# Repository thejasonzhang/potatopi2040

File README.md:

PotatoPi
Overview

PotatoPi is a custom RP2040-based devboard that can be used for lots of cool hardware and software projects.
It follows the same pinout as the Raspberry Pi Pico and is fully feature-compatible.

It will also include headers soldered on.

- Features
- 16MB onboard flash memory
- Convenient reset button for easy flashing
- Custom PotatoPi artwork on both sides of the PCB
- All components hand soldered (no PCBA)

I made this to get back into hardware and to redeem myself from my last project.
I also wanted to try out SMD soldering.
The board will use a hot plate to do most of the reflow work and then an iron to fix any mistakes and add the ehaders.

Gallery

Front & board renders as well as Potato Pi illustrations:

Bill of Materials (BOM)

| **Category** | **Designator / Item** | **Footprint / Description** | **Qty** | **Value / Part** | **Link**                                                                                                 | **Cost** |
| ------------ | --------------------- | --------------------------- | ------- | ---------------- | -------------------------------------------------------------------------------------------------------- | -------- |
| Capacitor    | C1, C12               | 402                         | 2       | 1µF              | [https://www.lcsc.com/product-detail/C29266.html](https://www.lcsc.com/product-detail/C29266.html)       | 0.26     |
| Capacitor    | C10–C11, C17, C2–C9   | 402                         | 11      | 0.1µF            | [https://www.lcsc.com/product-detail/C1525.html](https://www.lcsc.com/product-detail/C1525.html)         | 0.13     |
| Capacitor    | C13, C14              | 603                         | 2       | 10µF             | [https://www.lcsc.com/product-detail/C19702.html](https://www.lcsc.com/product-detail/C19702.html)       | 0.40     |
| Capacitor    | C15, C16              | 603                         | 2       | 33pF             | [https://www.lcsc.com/product-detail/C107047.html](https://www.lcsc.com/product-detail/C107047.html)     | 0.30     |
| Connector    | J1                    | USB-C Receptacle            | 1       | USB 2.0 14P      | [https://www.lcsc.com/product-detail/C165948.html](https://www.lcsc.com/product-detail/C165948.html)     | 0.85     |
| Connector    | J2, J3                | Pin Header 1x20             | 2       | Conn_01x20       | [https://www.lcsc.com/product-detail/C42431804.html](https://www.lcsc.com/product-detail/C42431804.html) | 0.46     |
| Connector    | J4                    | Pin Header 1x03             | 1       | Conn_01x03       | [https://www.lcsc.com/product-detail/C32713269.html](https://www.lcsc.com/product-detail/C32713269.html) | 0.11     |
| Resistor     | R1, R2                | 402                         | 2       | 5.1kΩ            | [https://www.lcsc.com/product-detail/C25905.html](https://www.lcsc.com/product-detail/C25905.html)       | 0.08     |
| Resistor     | R3, R4                | 402                         | 2       | 27Ω              | [https://www.lcsc.com/product-detail/C25100.html](https://www.lcsc.com/product-detail/C25100.html)       | 0.08     |
| Resistor     | R5, R6                | 402                         | 2       | 1kΩ              | [https://www.lcsc.com/product-detail/C11702.html](https://www.lcsc.com/product-detail/C11702.html)       | 0.07     |
| Resistor     | R7                    | 402                         | 1       | 10kΩ             | [https://www.lcsc.com/product-detail/C60490.html](https://www.lcsc.com/product-detail/C60490.html)       | 0.08     |
| Switch       | SW1                   | Push Button                 | 1       | Momentary        | [https://www.lcsc.com/product-detail/C720477.html](https://www.lcsc.com/product-detail/C720477.html)     | 0.55     |
| IC           | U1                    | QFN-56                      | 1       | RP2040           | [https://www.lcsc.com/product-detail/C2040.html](https://www.lcsc.com/product-detail/C2040.html)         | 0.95     |
| IC           | U2                    | SOT-23                      | 1       | MCP1700-3302     | [https://www.lcsc.com/product-detail/C39051.html](https://www.lcsc.com/product-detail/C39051.html)       | 2.45     |
| IC           | U3                    | USON-8                      | 1       | W25Q16JV         | [https://www.lcsc.com/product-detail/C2456208.html](https://www.lcsc.com/product-detail/C2456208.html)   | 1.31     |
| Crystal      | Y1                    | 3225                        | 1       | 12 MHz           | [https://www.lcsc.com/product-detail/C9002.html](https://www.lcsc.com/product-detail/C9002.html)         | 0.73     |
| Service      | PCB                   | JLCPCB fabrication          | 1       | Manufacturing    | [https://cart.jlcpcb.com/quote/gerberviewThree/?qs=d00311a2c2824fc7aa7ee1bc072ff726_1_0_1_0_0.html]                                                                                                     | 2.10     |
| Tool         | Tip                   | T18-D24 solder tip          | 1       | Hakko chisel     | [https://www.microcenter.com/product/658966/hakko-t18-series-006-in-chisel-tip]                                                                                            | 6.99     |
| Tool         | Wick                  | Desolder wick               | 1       | iFixit wick      |[https://www.microcenter.com/product/693022/ifixit-desoldering-wick]                                                                                            | 4.99     |
| Tool         | Tweezers              | Curved ESD                  | 1       | precision        | [https://www.microcenter.com/product/361636/enkay-products-heat-resistant-soldering-tweezers-curved-point]                                                                                             | 2.99     |
| Tool         | Helping Hand          | Magnifier stand             | 1       | third hand       |[https://www.microcenter.com/product/618902/inland-inland-adjustable-helping-hand-w-magnifying-glass]                                                                                             | 4.99     |
Cost Summary
Subtotal: $30.87
Shipping: $15.24
Tax: $3.82
TOTAL: $49.93

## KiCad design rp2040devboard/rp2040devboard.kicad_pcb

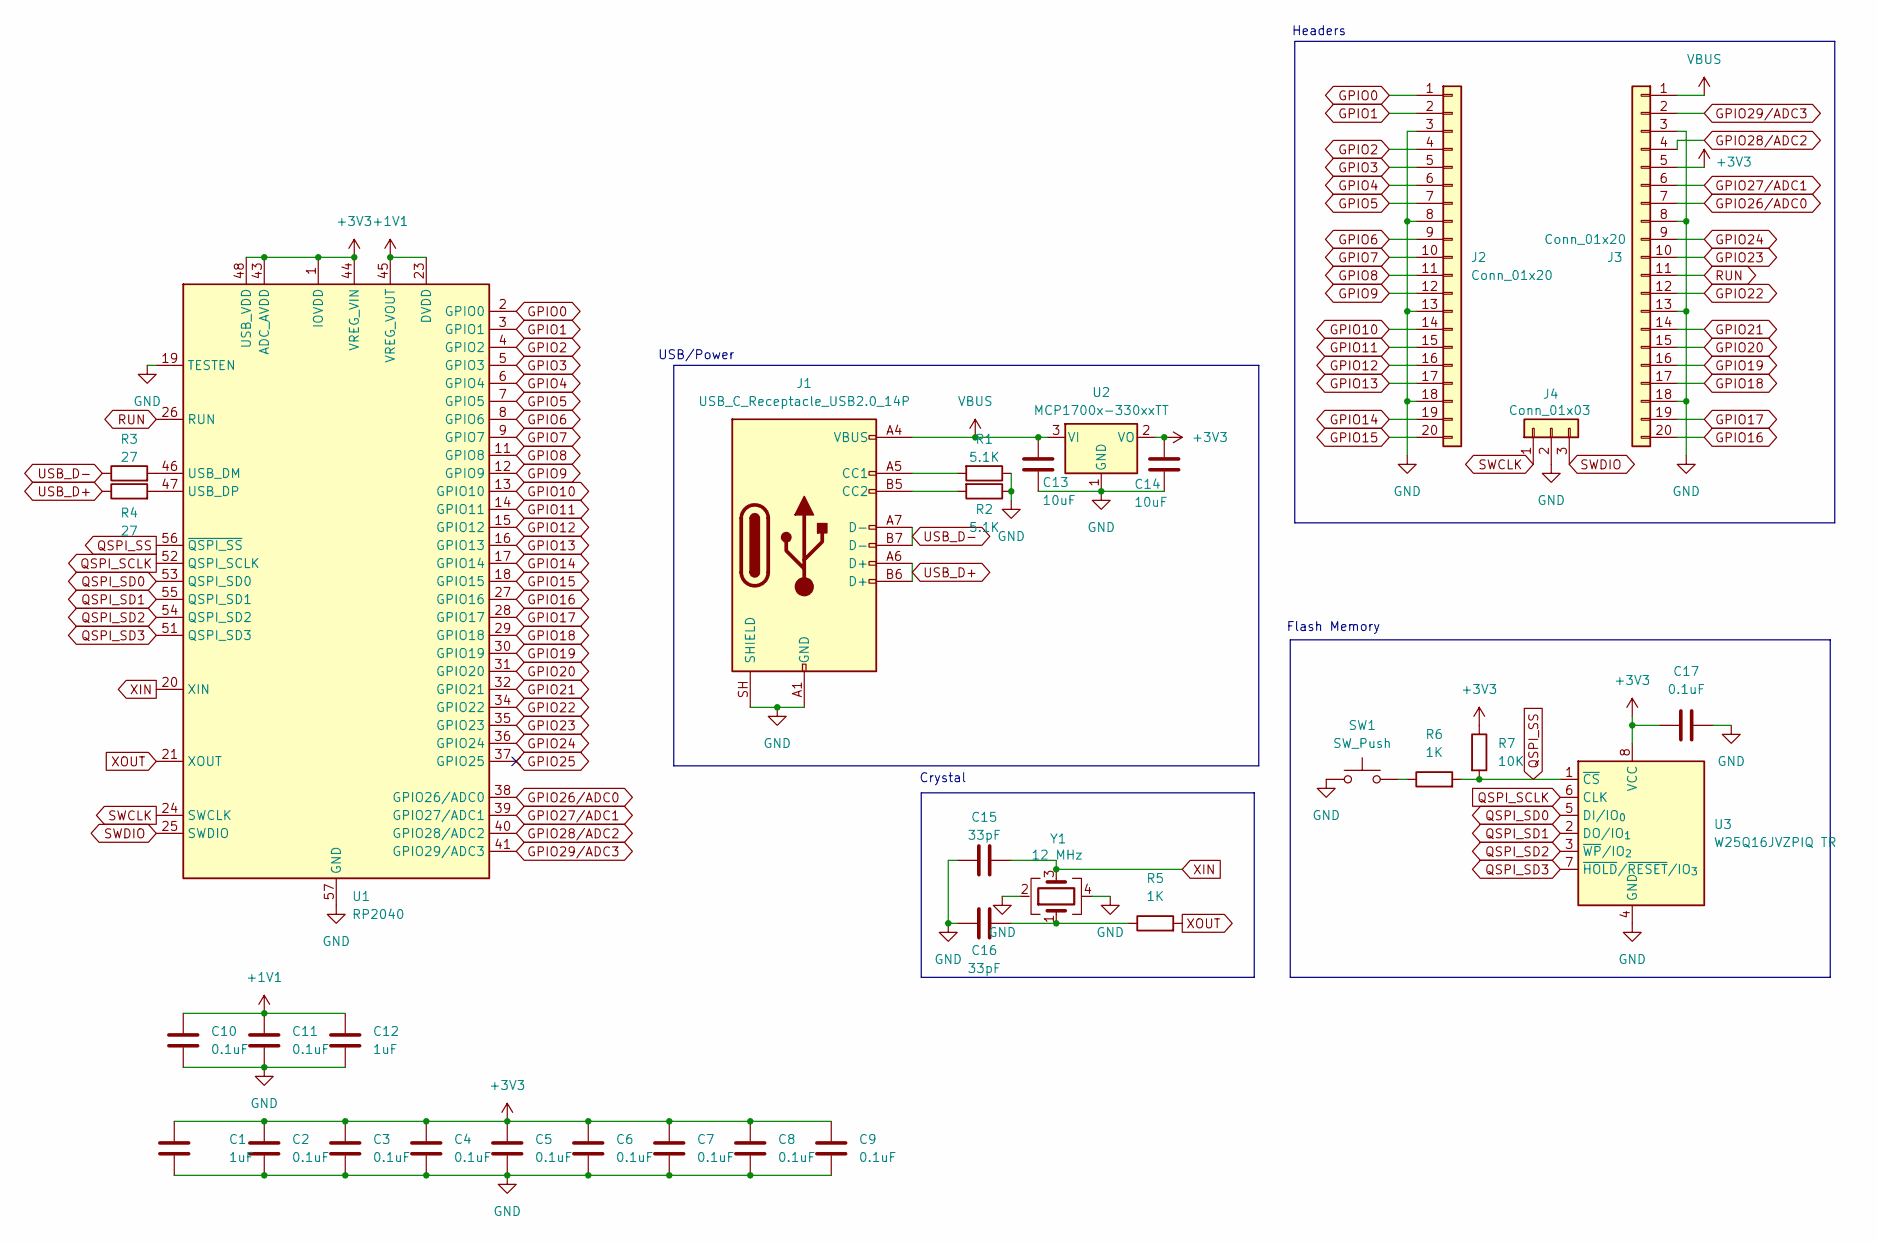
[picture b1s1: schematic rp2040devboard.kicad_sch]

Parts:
C1, C12: 1uF; C_0402_1005Metric
C2, C3, C4, C5, C6, C7, C8, C9, C10, C11, C17: 0.1uF; C_0402_1005Metric
C13, C14: 10uF; C_0603_1608Metric
C15, C16: 33pF; C_0603_1608Metric
J1: USB_C_Receptacle_USB2.0_14P; USB_C_Receptacle_HRO_TYPE-C-31-M-12
J2, J3: Conn_01x20; PinHeader_1x20_P2.54mm_Vertical
J4: Conn_01x03; PinHeader_1x03_P2.54mm_Vertical
R1, R2: 5.1K; R_0402_1005Metric
R3, R4: 27; R_0402_1005Metric
R5, R6: 1K; R_0402_1005Metric
R7: 10K; R_0402_1005Metric
SW1: SW_Push; SW_Push_SPST_NO_Alps_SKRK
U1: RP2040; QFN-56-1EP_7x7mm_P0.4mm_EP3.2x3.2mm
U2: MCP1700x-330xxTT; SOT-23
U3: W25Q16JVZPIQ TR; Winbond_USON-8-1EP_3x2mm_P0.5mm_EP0.2x1.6mm
Y1: 12 MHz; Crystal_SMD_3225-4Pin_3.2x2.5mm

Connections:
+1V1: C10.1, C11.1, C12.1, U1.23 (DVDD), U1.45 (VREG_VOUT), U1.50 (DVDD)
+3V3: C1.1, C2.1, C3.1, C4.1, C5.1, C6.1, C7.1, C8.1, C9.1, C14.1, C17.2, J3.5, R7.1, U1.1 (IOVDD), U1.10 (IOVDD), U1.22 (IOVDD), U1.33 (IOVDD), U1.42 (IOVDD), U1.43 (ADC_AVDD), U1.44 (VREG_VIN), U1.48 (USB_VDD), U1.49 (IOVDD), U2.2 (VO), U3.8 (VCC)
GND: C1.2, C2.2, C3.2, C4.2, C5.2, C6.2, C7.2, C8.2, C9.2, C10.2, C11.2, C12.2, C13.1, C14.2, C15.1, C16.1, C17.1, J1.A1 (GND), J1.A12 (GND), J1.B1 (GND), J1.B12 (GND), J1.SH (SHIELD), J2.3, J2.8, J2.13, J2.18, J3.3, J3.8, J3.13, J3.18, J4.2, R1.1, R2.1, SW1.1, U1.19 (TESTEN), U1.57 (GND), U2.1 (GND), U3.4 (GND), Y1.2 (G), Y1.4 (G)
GPIO0: J2.1, U1.2 (GPIO0)
GPIO1: J2.2, U1.3 (GPIO1)
GPIO2: J2.4, U1.4 (GPIO2)
GPIO3: J2.5, U1.5 (GPIO3)
GPIO4: J2.6, U1.6 (GPIO4)
GPIO5: J2.7, U1.7 (GPIO5)
GPIO6: J2.9, U1.8 (GPIO6)
GPIO7: J2.10, U1.9 (GPIO7)
GPIO8: J2.11, U1.11 (GPIO8)
GPIO9: J2.12, U1.12 (GPIO9)
GPIO10: J2.14, U1.13 (GPIO10)
GPIO11: J2.15, U1.14 (GPIO11)
GPIO12: J2.16, U1.15 (GPIO12)
GPIO13: J2.17, U1.16 (GPIO13)
GPIO14: J2.19, U1.17 (GPIO14)
GPIO15: J2.20, U1.18 (GPIO15)
GPIO16: J3.20, U1.27 (GPIO16)
GPIO17: J3.19, U1.28 (GPIO17)
GPIO18: J3.17, U1.29 (GPIO18)
GPIO19: J3.16, U1.30 (GPIO19)
GPIO20: J3.15, U1.31 (GPIO20)
GPIO21: J3.14, U1.32 (GPIO21)
GPIO22: J3.12, U1.34 (GPIO22)
GPIO23: J3.10, U1.35 (GPIO23)
GPIO24: J3.9, U1.36 (GPIO24)
GPIO25: U1.37 (GPIO25)
GPIO26/ADC0: J3.7, U1.38 (GPIO26/ADC0)
GPIO27/ADC1: J3.6, U1.39 (GPIO27/ADC1)
GPIO28/ADC2: J3.4, U1.40 (GPIO28/ADC2)
GPIO29/ADC3: J3.2, U1.41 (GPIO29/ADC3)
unnamed: C16.2, R5.1, Y1.1
unnamed: J1.A5 (CC1), R1.2
unnamed: J1.B5 (CC2), R2.2
unnamed: R6.1, SW1.2
unnamed: R3.2, U1.46 (USB_DM)
unnamed: R4.2, U1.47 (USB_DP)
QSPI_SCLK: U1.52 (QSPI_SCLK), U3.6 (CLK)
QSPI_SD0: U1.53 (QSPI_SD0), U3.5 (DI/IO_{0})
QSPI_SD1: U1.55 (QSPI_SD1), U3.2 (DO/IO_{1})
QSPI_SD2: U1.54 (QSPI_SD2), U3.3 (~WP/IO_{2})
QSPI_SD3: U1.51 (QSPI_SD3), U3.7 (~HOLD/~RESET/IO_{3})
QSPI_SS: R6.2, R7.2, U1.56 (~QSPI_SS), U3.1 (~CS)
RUN: J3.11, U1.26 (RUN)
SWCLK: J4.1, U1.24 (SWCLK)
SWDIO: J4.3, U1.25 (SWDIO)
USB_D+: J1.A6 (D+), J1.B6 (D+), R4.1
USB_D-: J1.A7 (D-), J1.B7 (D-), R3.1
VBUS: C13.2, J1.A4 (VBUS), J1.A9 (VBUS), J1.B4 (VBUS), J1.B9 (VBUS), J3.1, U2.3 (VI)
XIN: C15.2, U1.20 (XIN), Y1.3
XOUT: R5.2, U1.21 (XOUT)

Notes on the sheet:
USB/Power
Crystal
Flash Memory
Headers

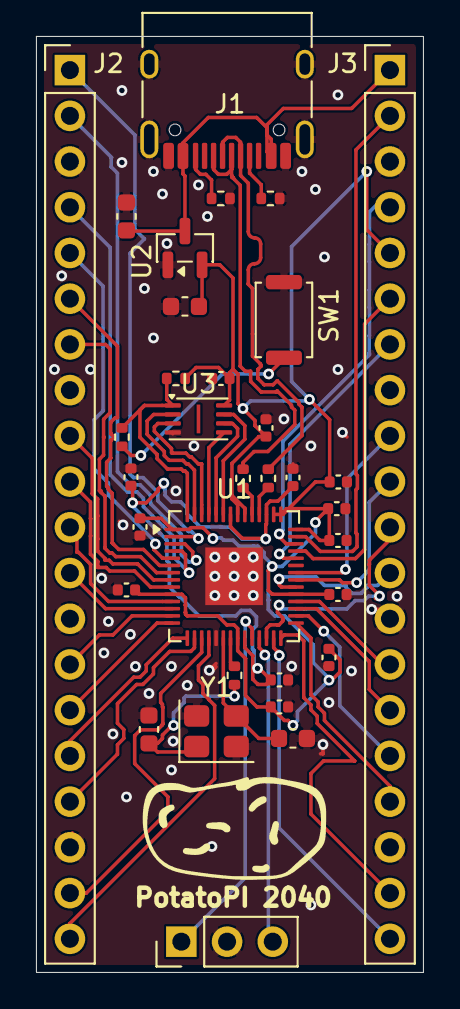
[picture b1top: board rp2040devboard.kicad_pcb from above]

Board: 2 copper layers, 21.5 x 52.0 mm, 33 parts (0 on the bottom side), 52 nets.

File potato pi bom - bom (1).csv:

Designator,Footprint,Quantity,Value,link,Unir Cost,Cost,Column 1
"C1, C12",402,2,1uF,https://www.lcsc.com/product-detail/C29266.html?s_z=n_1uF&sp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,0.0026*100=0.26,0.26,TRUE
"C10, C11, C17, C2, C3, C4, C5, C6, C7, C8, C9",402,11,0.1uF,https://www.lcsc.com/product-detail/C1525.html?s_z=n_CL05B10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,0.0013*100=0.13,0.13,TRUE
"C13, C14",603,2,10uF,https://www.lcsc.com/product-detail/C19702.html?s_z=n_10uF&s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,0.008*50=0.4,0.4,TRUE
"C15, C16",603,2,33pF,https://www.lcsc.com/product-detail/C107047.html?s_z=n_33pF&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,0.003*100=0.3,0.3,TRUE
J1,USB_C_Receptacle_HRO_TYPE-C-31-M-12,1,USB_C_Receptacle_USB2.0_14P,https://www.lcsc.com/product-detail/C165948.html?s_z=n_TYPE-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,0.17*5=0.85,0.85,TRUE
"J2, J3",PinHeader_1x20_P2.54mm_Vertical,2,Conn_01x20,https://www.lcsc.com/product-detail/C42431804.html?s_z=n_1x2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,0.092*5=0.46,0.46,TRUE
J4,PinHeader_1x03_P2.54mm_Vertical,1,Conn_01x03,https://www.lcsc.com/product-detail/C32713269.html?s_z=n_1x3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,0.0228*5=0.11,0.11,TRUE
"R1, R2",402,2,5.1K,https://www.lcsc.com/product-detail/C25905.html?s_z=n_0402WG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,0.0008*100=0.08,0.08,TRUE
"R3, R4",402,2,27ohm,https://www.lcsc.com/product-detail/C25100.html?s_z=n_27ohm&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,0.0008*100=0.08,0.08,TRUE
"R5, R6",402,2,1K,https://www.lcsc.com/product-detail/C11702.html?s_z=n_0402WG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,0.0007*100=0.07,0.07,TRUE
R7,402,1,10K,https://www.lcsc.com/product-detail/C60490.html?s_z=n_10k%25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,0.0008*100=0.08,0.08,TRUE
SW1,SW_Push_SPST_NO_Alps_SKRK,1,SW_Push,https://www.lcsc.com/product-detail/C720477.html?s_z=n_TS-10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,0.055*10=0.55,0.55,TRUE
U1,QFN-56-1EP_7x7mm_P0.4mm_EP3.2x3.2mm,1,RP2040,https://www.lcsc.com/product-detail/C2040.html?s_z=n_rp2040&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,0.95,0.95,TRUE
U2,SOT-23,1,MCP1700x-330xxTT,https://www.lcsc.com/product-detail/C39051.html?s_z=n_MCP170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,0.49*5=2.45,2.45,TRUE
U3,Winbond_USON-8-1EP_3x2mm_P0.5mm_EP0.2x1.6mm,1,W25Q16JVZPIQ TR,https://www.lcsc.com/product-detail/C2456208.html?s_z=n_W25Q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,1.31,1.31,TRUE
Y1,Crystal_SMD_3225-4Pin_3.2x2.5mm,1,12 MHz,https://www.lcsc.com/product-detail/C9002.html?s_z=n_X322512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,0.073*10=0.73,0.73,TRUE
,JLCPCB,1,,https://cart.jlcpcb.com/quote/gerberviewThree/?qs=a23e7f3868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,2.1,2.1,TRUE
,T18-D24 Tip,1,,Hakko T18 Series 0.09 in. Chisel Tip - Micro Center,6.99,6.99,TRUE
,Wick,1,,iFixit Desoldering Wick - Micro Center,4.99,4.99,TRUE
,Rosin Flux,n/a,,CAIG Laboratories DeoxIT Brand No Clean RMA Soldering Flux in Syringe Applicator - Micro Center,7.99,0,TRUE
,Tweezers,1,,https://www.microcenter.com/product/361636/enkay-products-he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,2.99,2.99,TRUE
,Helping Hand and Magnifying Glass,1,,Inland Inland Adjustable Helping Hand w/ Magnifying Glass - Micro Center,4.99,4.99,TRUE
,,,,,,,
,,,,,Subtotal,,
,,,,,,30.87,
,,,,,Shipping and Handling,,
,,,,,LCSC,12.12,
,,,,,JLCPCB,3.12,
,,,,,,,
,,,,,Tax,,
,,,,,Micro Center,3.82,
,,,,,,,
,,,,,Total,,
,,,,,,49.93,

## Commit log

2026-04-14 Remove an image from the README gallery
    Removed an image from the gallery section.
2026-04-14 updated ground via design for mcu
    easier to hand solder as you can feed solder through the via
